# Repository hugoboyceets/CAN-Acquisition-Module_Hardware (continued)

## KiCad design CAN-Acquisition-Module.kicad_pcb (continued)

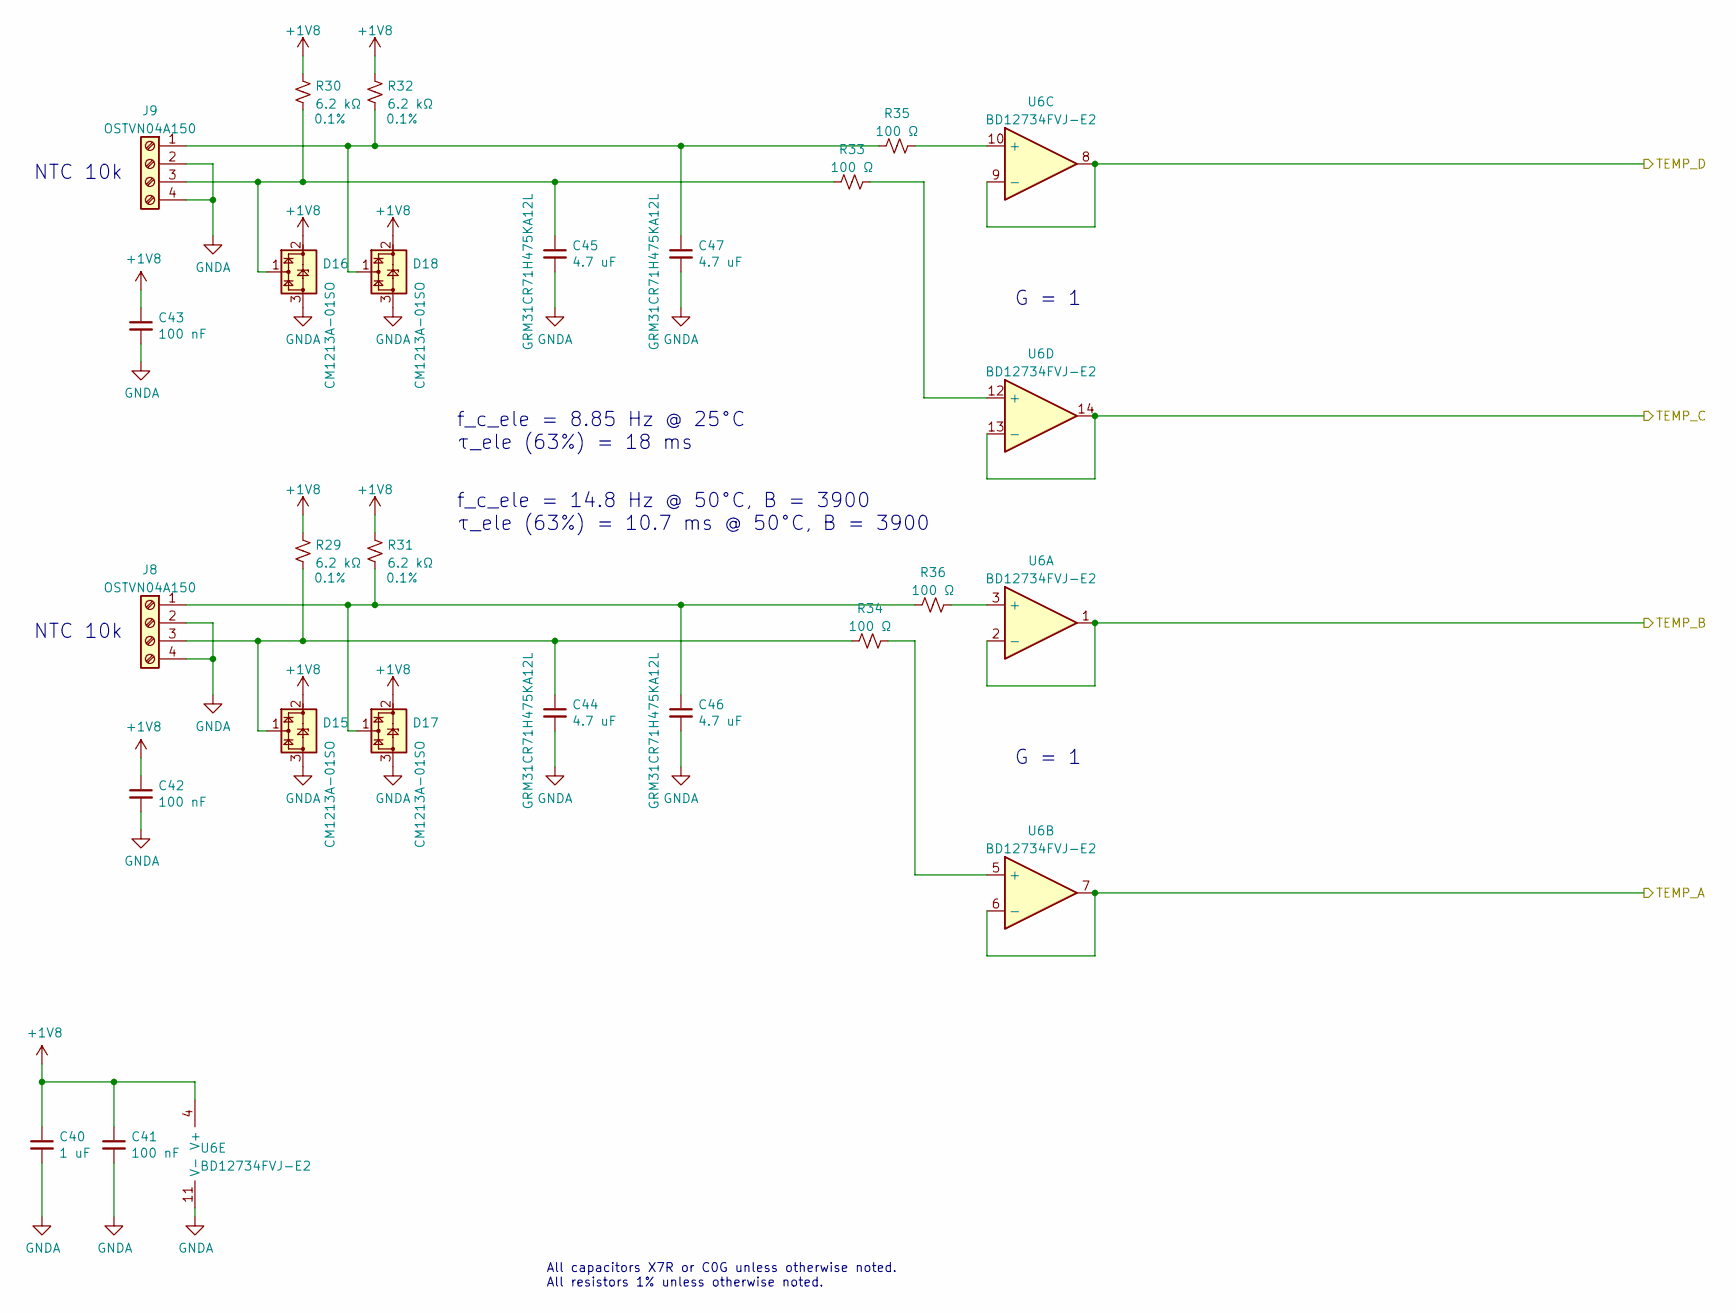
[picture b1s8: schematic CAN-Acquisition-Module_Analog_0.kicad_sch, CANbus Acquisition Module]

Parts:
C40: 1 uF; C_0603_1608Metric; Rated Voltage 25V; LCSC P/N C386079
C41, C42, C43: 100 nF; C_0402_1005Metric; Rated Voltage 16V; LCSC P/N C77014
C44, C45, C46, C47: 4.7 uF; C_1206_3216Metric; Rated Voltage 50V; LCSC P/N C92853
D15, D16, D17, D18: CM1213A-01SO; SOT-23; LCSC P/N C558429
J8, J9: OSTVN04A150; LCSC P/N C708735
R29, R30, R31, R32: 6.2 kΩ; R_0805_2012Metric; Tolerance 0.1%; LCSC P/N C351551
R33, R34, R35, R36: 100 Ω; R_0603_1608Metric; Tolerance 1%; LCSC P/N C105588
U6: BD12734FVJ-E2; TSSOP-14_4.4x5mm_P0.65mm; LCSC P/N C693071

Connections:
+1V8: C40.1, C41.1, C42.1, C43.1, D15.2 (VP), D16.2 (VP), D17.2 (VP), D18.2 (VP), R29.1, R30.1, R31.1, R32.1, U6.4 (V+); also elsewhere on the board
/ADC0: U6.6 (-), U6.7; also elsewhere on the board
/ADC1: U6.1, U6.2 (-); also elsewhere on the board
/ADC2: U6.13 (-), U6.14; also elsewhere on the board
/ADC3: U6.8, U6.9 (-); also elsewhere on the board
GNDA: C40.2, C41.2, C42.2, C43.2, C44.2, C45.2, C46.2, C47.2, D15.3 (VN), D16.3 (VN), D17.3 (VN), D18.3 (VN), J8.2, J8.4, J9.2, J9.4, U6.11 (V-); also elsewhere on the board
unnamed: C44.1, D15.1 (CH1), J8.3, R29.2, R34.2
unnamed: C45.1, D16.1 (CH1), J9.3, R30.2, R33.2
unnamed: C46.1, D17.1 (CH1), J8.1, R31.2, R36.2
unnamed: C47.1, D18.1 (CH1), J9.1, R32.2, R35.2
unnamed: R33.1, U6.12 (+)
unnamed: R34.1, U6.5 (+)
unnamed: R35.1, U6.10 (+)
unnamed: R36.1, U6.3 (+)

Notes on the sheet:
NTC 10k
All capacitors X7R or C0G unless otherwise noted. All resistors 1% unless otherwise noted.
f_c_ele = 14.8 Hz @ 50°C, B = 3900 τ_ele (63%) = 10.7 ms @ 50°C, B = 3900
G = 1
f_c_ele = 8.85 Hz @ 25°C τ_ele (63%) = 18 ms

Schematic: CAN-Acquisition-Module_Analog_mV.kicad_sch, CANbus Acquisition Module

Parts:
C51, C55, C56, C57, C58: 1 uF; C_0603_1608Metric; Rated Voltage 25V; LCSC P/N C386079
C52, C53, C54: 100 nF; C_0402_1005Metric; Rated Voltage 16V; LCSC P/N C77014
D21, D22, D23, D24: CM1213A-01SO; SOT-23; LCSC P/N C558429
J10, J11: OSTVN04A150; LCSC P/N C708735
R52, R53, R54, R55: 10 kΩ; R_0603_1608Metric; Tolerance 1%; LCSC P/N C98220
R56, R57, R58, R59: Ω; R_0603_1608Metric; LCSC P/N DNP
R60, R61, R62, R63: 1 kΩ; R_0603_1608Metric; Tolerance 1%; LCSC P/N C22548
R64, R65, R66, R67: 2 kΩ; R_0603_1608Metric; Tolerance 1%; LCSC P/N C22975
R68, R69, R70, R71: 47 kΩ; R_0603_1608Metric; Tolerance 1%; LCSC P/N C105579
U9: OPA4317IPWR; TSSOP-14_4.4x5mm_P0.65mm; LCSC P/N C783605

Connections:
+1V8: C51.1, C52.1, C53.1, C54.1, D21.2 (VP), D22.2 (VP), D23.2 (VP), D24.2 (VP), U9.4 (V+); also elsewhere on the board
/ADC8: R68.2, U9.7; also elsewhere on the board
/ADC9: R71.2, U9.1; also elsewhere on the board
/ADC10: R70.2, U9.14; also elsewhere on the board
/ADC11: R69.2, U9.8; also elsewhere on the board
GNDA: C51.2, C52.2, C53.2, C54.2, C55.2, C56.2, C57.2, C58.2, D21.3 (VN), D22.3 (VN), D23.3 (VN), D24.3 (VN), J10.2, J10.4, J11.2, J11.4, R56.2, R57.2, R58.2, R59.2, R60.1, R61.1, R62.1, R63.1, U9.11 (V-); also elsewhere on the board
unnamed: C55.1, R53.2, R56.1, U9.5 (+)
unnamed: C56.1, R55.2, R57.1, U9.12 (+)
unnamed: C57.1, R52.2, R58.1, U9.3 (+)
unnamed: C58.1, R54.2, R59.1, U9.10 (+)
unnamed: D21.1 (CH1), J10.3, R53.1
unnamed: D22.1 (CH1), J11.3, R55.1
unnamed: D23.1 (CH1), J10.1, R52.1
unnamed: D24.1 (CH1), J11.1, R54.1
unnamed: R60.2, R64.1, U9.2 (-)
unnamed: R61.2, R65.1, U9.6 (-)
unnamed: R62.2, R66.1, U9.9 (-)
unnamed: R63.2, R67.1, U9.13 (-)
unnamed: R64.2, R71.1
unnamed: R65.2, R68.1
unnamed: R66.2, R69.1
unnamed: R67.2, R70.1

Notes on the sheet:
All capacitors X7R or C0G unless otherwise noted. All resistors 1% unless otherwise noted.
Other good cheap zero-drift op-amp: NCS21874/NCV21874
0-36 mV
G = 50
fc_ele = 15.9 Hz τ_ele (63%) = 10 ms

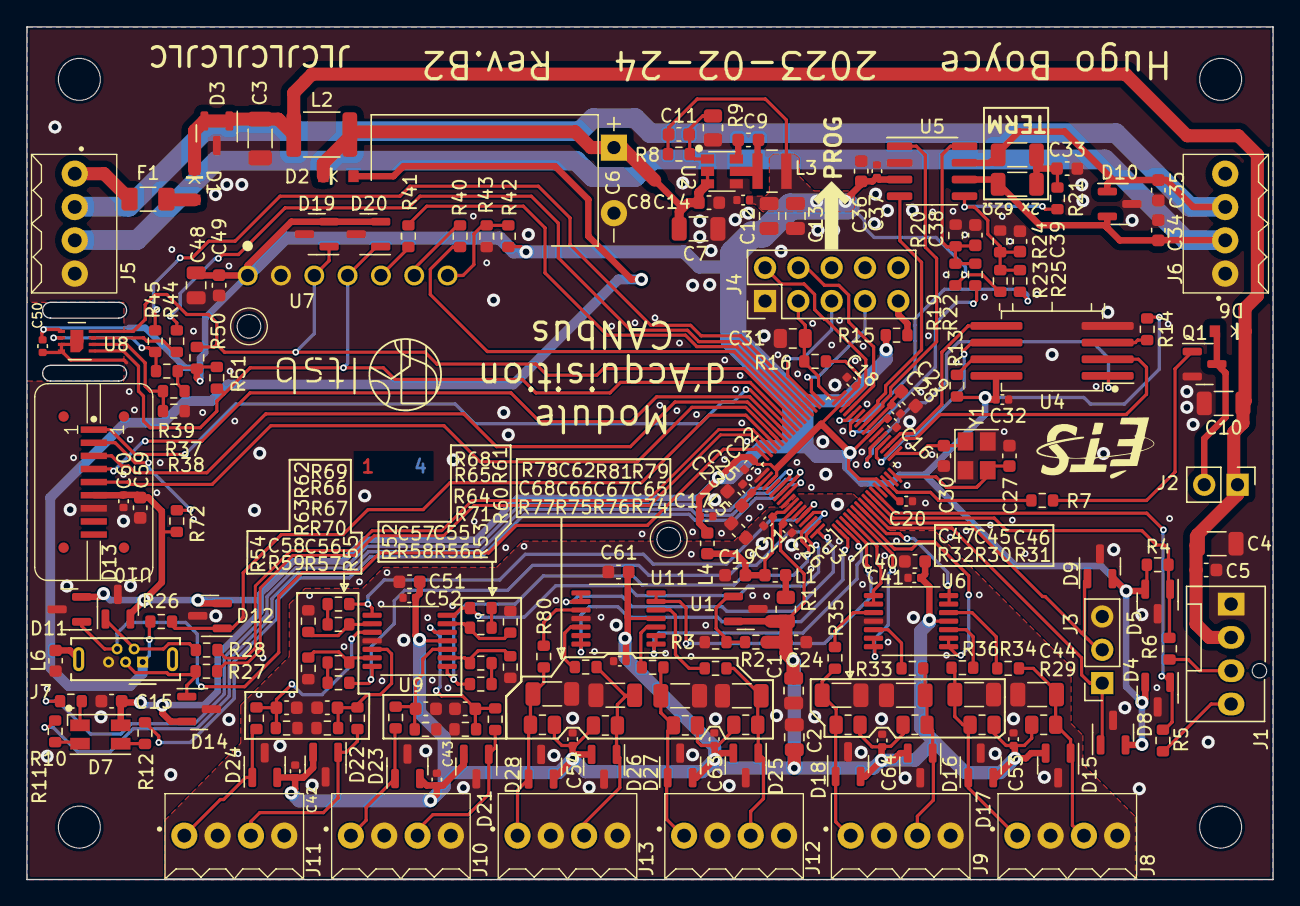
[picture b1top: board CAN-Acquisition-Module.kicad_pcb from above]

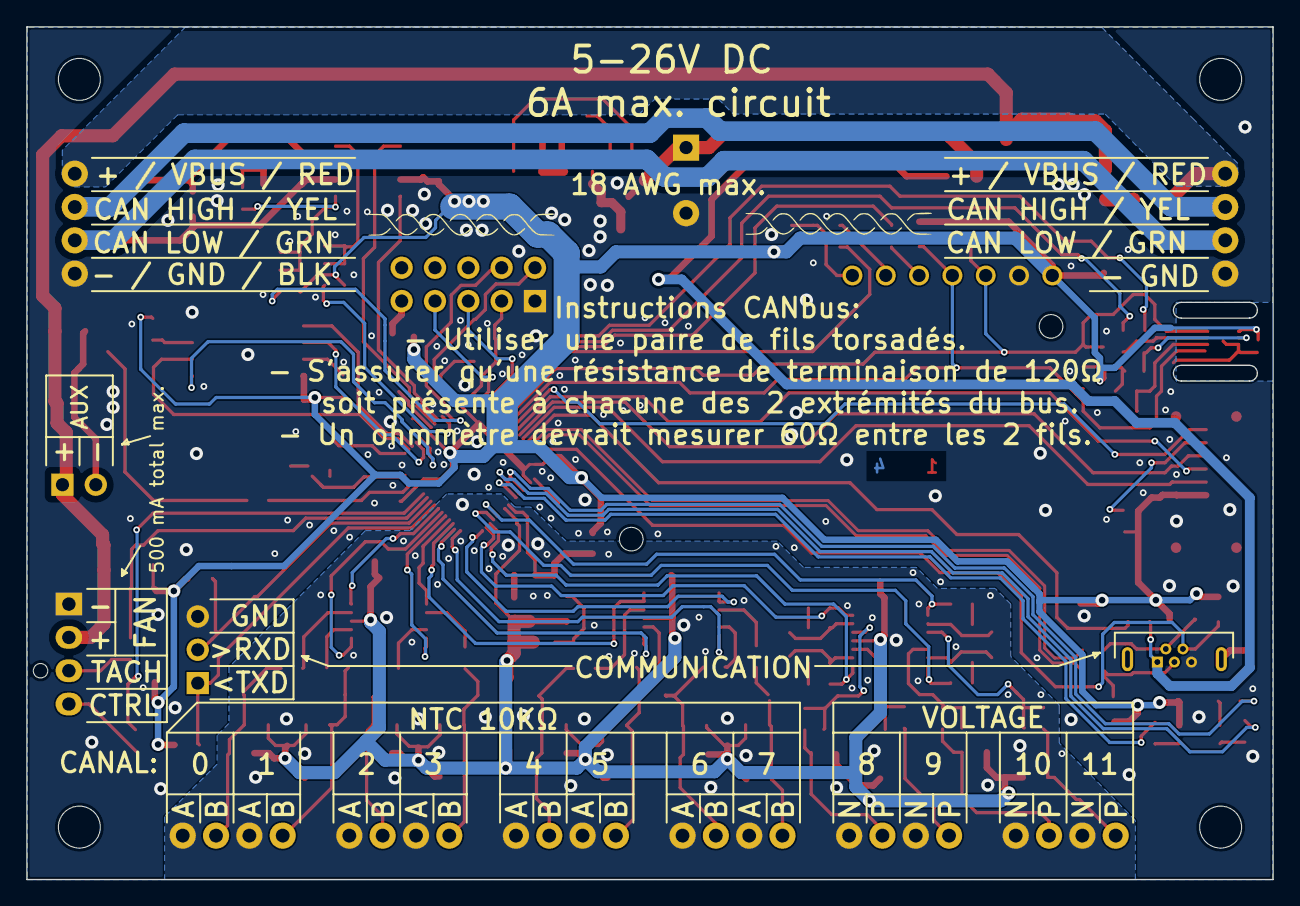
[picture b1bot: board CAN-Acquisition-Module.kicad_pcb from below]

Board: 4 copper layers, 95.0 x 65.0 mm, 214 parts (2 on the bottom side), 124 nets.

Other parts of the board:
C61: 1 uF; C_0603_1608Metric
C62, C63, C64: 100 nF; C_0402_1005Metric
C65, C66, C67, C68: 4.7 uF; C_1206_3216Metric
D25, D26, D27, D28: CM1213A-01SO; SOT-23
G1, G2, G5, G5#2: LOGO
J12, J13: OSTVN04A150
R74, R75, R76, R77: 6.2 kΩ; R_0805_2012Metric
R78, R79, R80, R81: 100 Ω; R_0603_1608Metric
U11: BD12734FVJ-E2; TSSOP-14_4.4x5mm_P0.65mm

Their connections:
+1V8: C61.1, C62.1, C63.1, C64.1, D25.2 (VP), D26.2 (VP), D27.2 (VP), D28.2 (VP), R74.1, R75.1, R76.1, R77.1, U11.4 (V+); also elsewhere on the board
/ADC4: U11.6 (-), U11.7; also elsewhere on the board
/ADC5: U11.1, U11.2 (-); also elsewhere on the board
/ADC6: U11.13 (-), U11.14; also elsewhere on the board
/ADC7: U11.8, U11.9 (-); also elsewhere on the board
GNDA: C61.2, C62.2, C63.2, C64.2, C65.2, C66.2, C67.2, C68.2, D25.3 (VN), D26.3 (VN), D27.3 (VN), D28.3 (VN), J12.2, J12.4, J13.2, J13.4, U11.11 (V-); also elsewhere on the board
unnamed: C65.1, D25.1 (CH1), J12.3, R74.2, R79.2
unnamed: C66.1, D26.1 (CH1), J13.3, R75.2, R78.2
unnamed: C67.1, D27.1 (CH1), J12.1, R76.2, R81.2
unnamed: C68.1, D28.1 (CH1), J13.1, R77.2, R80.2
unnamed: R78.1, U11.12 (+)
unnamed: R79.1, U11.5 (+)
unnamed: R80.1, U11.10 (+)
unnamed: R81.1, U11.3 (+)

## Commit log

2022-05-26 Initial files added
2022-05-26 Schematic started
    MCU section well advanced, power section started as well
2022-05-26 Added CAN page
    also power section has advanced
2022-05-27 Mid-day backup
2022-05-27 Advanced CAN section and "finished" power section
2022-05-30 Finished CAN section
2022-05-31 test
2022-05-31 Added stuff and cleanup
    Added LED, Power outputs, additional descriptions
2022-05-31 Added empty sheets
2022-06-01 Added analog and sensors sections
2022-06-02 Added screen sections and annotations
2022-06-03 PCB started
    Placement well advanced
2022-06-07 Added board settings
2022-06-07 Layout of analog section started
2022-06-09 Analog section, screen and USB finished
2022-06-10 Finished power outputs
2022-06-13 Only CAN transceiver left
    SPi flash should be added too
2022-06-13 forgor to save
2022-06-15 Rev. A1 release
2022-06-16 Added as-ordered P/Ns and regenerated Gerbers
2022-06-30 Rev. A2
    U1 had wrong pinout. NT1 label removed from silk. Green LED resistor increased in value
2022-07-05 Changed the node where the V_USB diode connects.
    Having the V_USB go through the VBUS inductor caused the voltage to sag too low.
2022-07-14 Rev. A2 started
    U1 had wrong pinout. NT1 label removed from silk. Green LED resistor increased in value
2022-07-14 Added TODO
    Route V_USB to C6, reduce screw terminal hole size, thermally isolate SHT3x sensor
2022-07-28 Rev.A2 pretty much finished
    V USB bypasses inductor L2
    Srew terminal pin holes size reduced
    Thermally isolated SHT3x
    Fixed U1 footprint
2022-07-28 Did not stage pcb during last commit. Oops!
2022-09-20 changed the date on the board for release A2
2022-09-20 Exported all files for A2 release
2022-10-03 Improved readme
2022-10-03 Fixed error in photo link
2022-10-03 Added more photos
2022-10-04 Fixed board and re-exported Gerbers. BOM is a WIP
    Some design rules were violated
2022-10-04 BOM updated for LCSC. Still a WIP.
2022-10-04 BOM updated for LCSC. Still a WIP
2022-10-05 Changed 47uF cap to 4.7uF
    Filtration can be done in software instead of hardware
2022-10-06 Added differential BOM for order (to be removed later)
2022-10-18 Added BOM diff for extra order
2022-10-19 Created Rev B1
    Replaced buck regulator S-8581AA with AP63200 because of shortage
2022-10-24 Exported pdfs and updated cartouche
2023-02-03 Created rev B2 to fix low pass filter specs
2023-02-03 Forgot to change project file
2023-02-25 Corrected U1 in schematic
2023-03-10 Improved ground trace width
